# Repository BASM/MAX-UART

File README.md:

MAX-UART
========

Stage: Stable

A board having convertor RX,TX and DTR,RTS pins.
The board was designed special for programming
Atmel AVR and NXP ARM microcontrollers.

Board used max3232 chip in SO16, used MOSFET transistors for
DTR, RTS level convert.

DTR and RTS used for Reset (ARM and AVR) and POI_3(for ARM).

Programs for programming is: 
* AVR -- Self  written from avr_boot project. 
  See https://github.com/BASM/avr_boot project.
* ARM -- lpc21isp. Project http://sourceforge.net/projects/lpc21isp/, https://github.com/Senseg/lpc21isp

CAD program is KiCAD.
Version 20130518 or newer.

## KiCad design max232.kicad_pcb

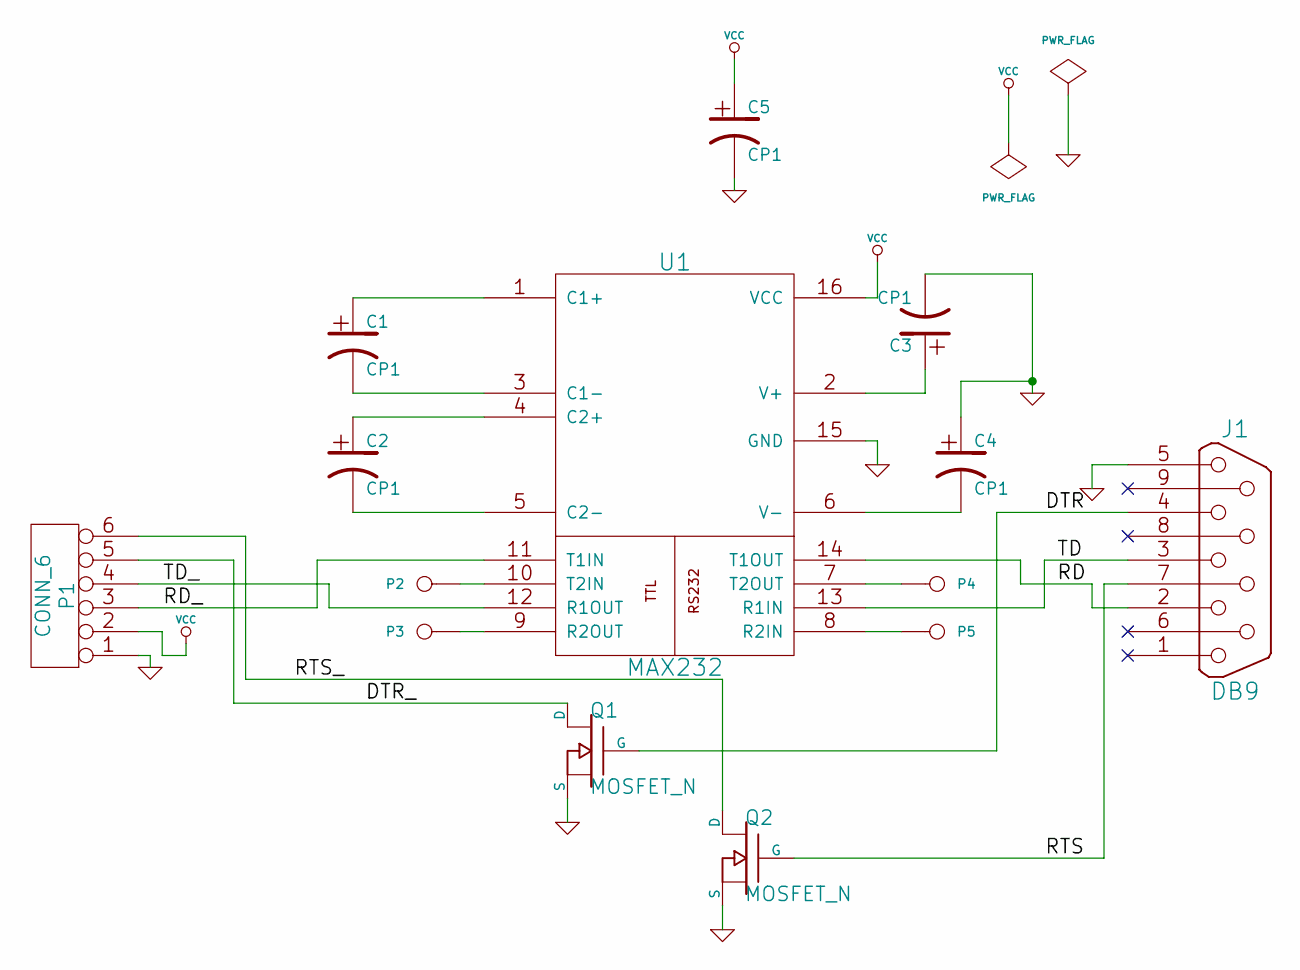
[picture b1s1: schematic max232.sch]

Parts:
C1, C2, C3, C4, C5: CP1
J1: DB9
P1: CONN_6
P2, P3, P4, P5: CONN_1
Q1, Q2: MOSFET_N
U1: MAX232

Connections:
/DTR: J1.4, Q1.G
/DTR_: P1.5, Q1.D
/RD: J1.2, U1.14 (T1OUT)
/RD_: P1.3, U1.11 (T1IN)
/RTS: J1.7, Q2.G
/RTS_: P1.6, Q2.D
/TD: J1.3, U1.13 (R1IN)
/TD_: P1.4, U1.12 (R1OUT)
GND: C3.2, C4.1, C5.2, J1.5, P1.1, Q1.S, Q2.S, U1.15 (GND)
unnamed: P5.1, U1.8 (R2IN)
unnamed: P2.1, U1.10 (T2IN)
unnamed: C3.1, U1.2 (V+)
unnamed: C4.2, U1.6 (V-)
unnamed: C2.1, U1.4 (C2+)
unnamed: C2.2, U1.5 (C2-)
unnamed: C1.2, U1.3 (C1-)
unnamed: C1.1, U1.1 (C1+)
unnamed: P3.1, U1.9 (R2OUT)
unnamed: P4.1, U1.7 (T2OUT)
VCC: C5.1, P1.2, U1.16 (VCC)

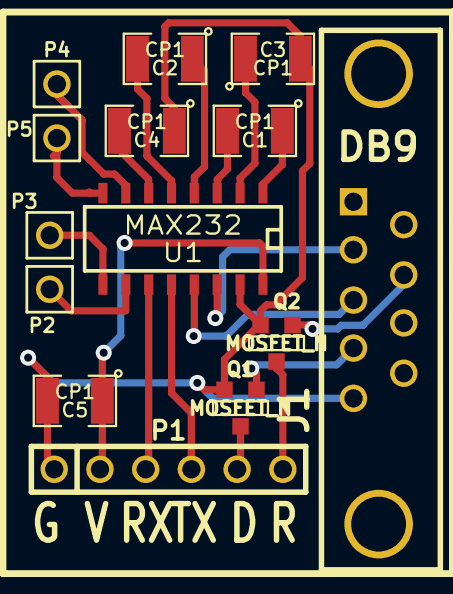
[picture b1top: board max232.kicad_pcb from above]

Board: 2 copper layers, 14 parts (0 on the bottom side), 20 nets.

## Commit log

2012-05-17 First release
2012-05-17 Added max232.brd, fixed uart.
2013-08-16 Pre fix variant for iStudio
2013-08-16 Version for iStudio.
2013-09-05 Added max3232 variant include DTR RTS output.
2013-09-05 Fixed schemantick.
2013-09-08 Fixed RX TX labels.
2013-09-20 Added new version format of pcb (new KiCAD). Fixed name DTR<->RTS.
2013-09-20 Removed project max3232, max232 include max3232.
2013-09-20 Fixed README
2013-09-20 Fix rename.sh script for new version of KiCAD
